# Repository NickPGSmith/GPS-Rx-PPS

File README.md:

# GPS-Rx-PPS
A KiCAD schematic and PCB to buffer/alarm a GPS receiver PPS signal

## Introduction

There are many cheap GPS receiver boards available which provide a serial output and Pulse-Per-Second (PPS) output, typically based on the uBlox 6 or later chip. This board is designed to take the PPS signal from such a receiver and provide buffering, LED drive, and missing pulse alarm (audio and LED).

For a printable schematic, see the file:
- GPS Rx PPS_sch.pdf

For a file to send to a fabricator (eg JLCPCB or PCBWay), use the file:
- Fabrication/GPS Rx PPS.zip

## uBlox Receiver Configuration

The uBlox receiver can be configured via the serial line using the [uCenter](https://www.u-blox.com/en/product/u-center) software. It should generate a 1 Hz outout (timed on falling edge) when GPS synchronisation has been obtained, otherwise a constant high to indicate failure:

View -> Configuration View; to activate change: Send

- TP5 (Timepulse 5)
    - PPS Settings for no GPS lock (use as an "alert" signal:
        - Frequency : 1 Hz
        - Duty Cycle : 0%
    - PPS Settings for GPS Locked:
        - Frequency Locked : 1 Hz
        - Duty Locked : 50%
    - Falling Edge on TOS

To save:
- CFG (Configuration)
    - Select: Save current configuration
    - Select in Devices: 2-I2C-EEPROM

## Circuit Description

The GPS receiver PPS signal is buffered by U2B to provide LED output, U2C to provide buffer drive for an external circuit, and the missing pulse detector built around U1. This will generate a low output after a few seconds of not receiving pulses; the timing can be adjusted by the combination of R3 and C4.

U2D and U2E provide an audio oscillator of a few kHz; its frequency can be adjusted by R9 and C6 to match the resonant frequncy of the piezo sounder used. The oscillator uses U2F as an output buffer/drive, with RV1 preset setting the desired volume.
The oscillations are quenched when Q2 is turned on, ie when the "Not Alarm" output of U1 is high.

PCB Connections:
- CON1: DC Power in (5 V)
- CON2: Power LED
- CON3: Alarm LED
- CON4: PPS in, from GPS received (timing on falling edge)
- CON5: PPS LED
- CON6: PPS out (jumper selects low impendance or 50 Ohm)
- CON7: Alarm sounder out

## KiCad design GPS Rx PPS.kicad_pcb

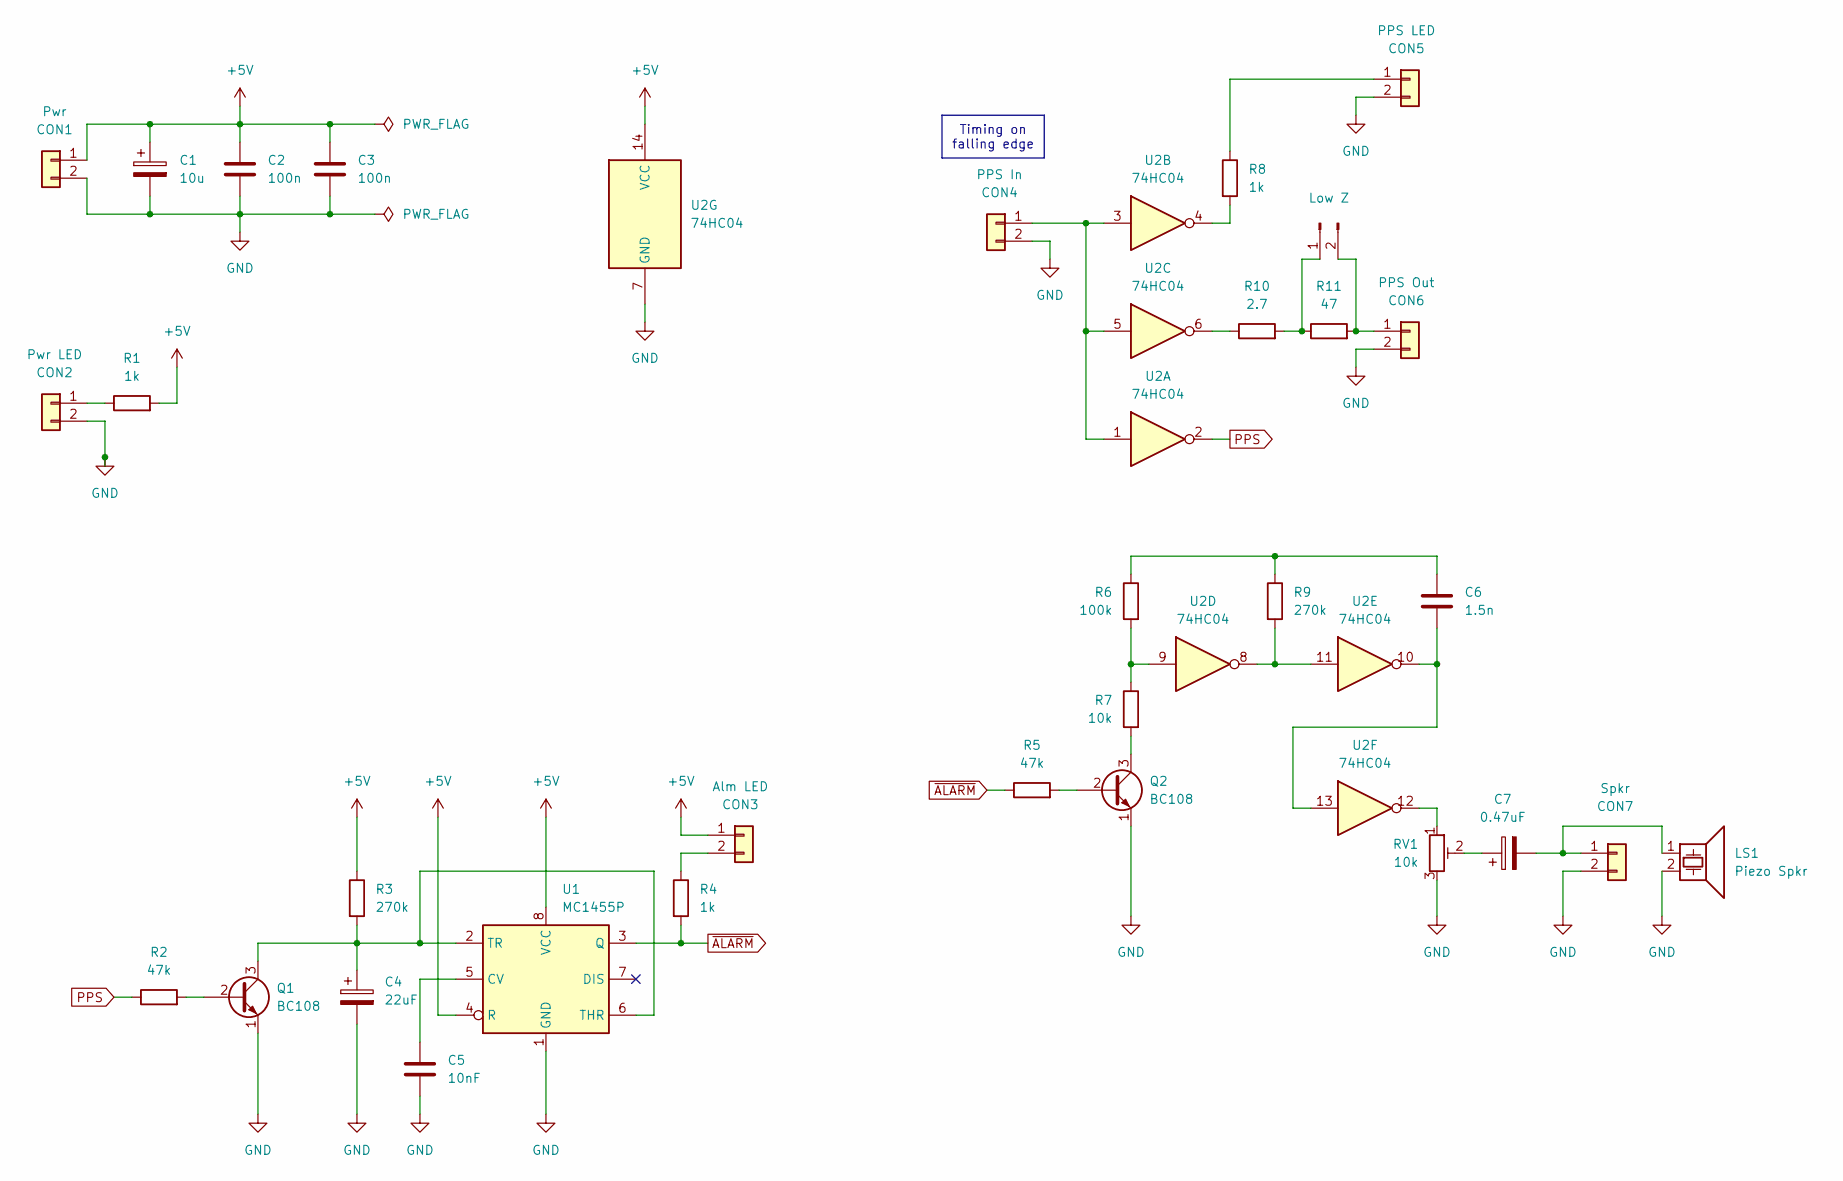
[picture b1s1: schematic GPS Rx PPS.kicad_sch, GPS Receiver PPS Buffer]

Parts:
C1: 10u; CP_Radial_D5.0mm_P2.00mm
C2, C3: 100n; C_Disc_D3.0mm_W1.6mm_P2.50mm
C4: 22uF; CP_Radial_D5.0mm_P2.00mm
C5: 10nF; C_Disc_D4.3mm_W1.9mm_P5.00mm
C6: 1.5n; C_Disc_D3.0mm_W1.6mm_P2.50mm
C7: 0.47uF; CP_Radial_D6.3mm_P2.50mm
CON1: Pwr; PinHeader_1x02_P2.54mm_Vertical
CON2: Pwr LED; PinHeader_1x02_P2.54mm_Vertical
CON3: Alm LED; PinHeader_1x02_P2.54mm_Vertical
CON4: PPS In; PinHeader_1x02_P2.54mm_Vertical
CON5: PPS LED; PinHeader_1x02_P2.54mm_Vertical
CON6: PPS Out; PinHeader_1x02_P2.54mm_Vertical
CON7: Spkr; PinHeader_1x02_P2.54mm_Vertical
J1: Low Z; PinHeader_1x02_P2.54mm_Vertical
LS1: Piezo Spkr; Buzzer_TDK_PS1240P02BT_D12.2mm_H6.5mm
Q1, Q2: BC108; TO-18-3
R1, R4, R8: 1k; R_Axial_DIN0207_L6.3mm_D2.5mm_P2.54mm_Vertical
R2, R5: 47k; R_Axial_DIN0207_L6.3mm_D2.5mm_P2.54mm_Vertical
R3, R9: 270k; R_Axial_DIN0207_L6.3mm_D2.5mm_P2.54mm_Vertical
R6: 100k; R_Axial_DIN0207_L6.3mm_D2.5mm_P2.54mm_Vertical
R7: 10k; R_Axial_DIN0207_L6.3mm_D2.5mm_P2.54mm_Vertical
R10: 2.7; R_Axial_DIN0207_L6.3mm_D2.5mm_P2.54mm_Vertical
R11: 47; R_Axial_DIN0207_L6.3mm_D2.5mm_P2.54mm_Vertical
RV1: 10k; Potentiometer_Piher_PT-6-V_Vertical
U1: MC1455P; DIP-8_W7.62mm_LongPads
U2: 74HC04; CERDIP-14_W7.62mm_SideBrazed_LongPads

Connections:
+5V: C1.1, C2.1, C3.1, CON1.1, CON3.1, R1.2, R3.1, U1.4 (R), U1.8 (VCC), U2.14 (VCC)
GND: C1.2, C2.2, C3.2, C4.2, C5.2, CON1.2, CON2.2, CON4.2, CON5.2, CON6.2, CON7.2, LS1.2, Q1.1 (E), Q2.1 (E), RV1.3, U1.1 (GND), U2.7 (GND)
unnamed: C6.1, R6.1, R9.1
unnamed: C6.2, U2.10, U2.13
unnamed: C7.1, RV1.2
unnamed: CON2.1, R1.1
unnamed: CON3.2, R4.1
unnamed: CON4.1, U2.1, U2.3, U2.5
unnamed: CON5.1, R8.1
unnamed: CON6.1, J1.2, R11.2
unnamed: C7.2, CON7.1, LS1.1
unnamed: J1.1, R10.2, R11.1
unnamed: Q1.2 (B), R2.2
unnamed: C4.1, Q1.3 (C), R3.2, U1.2 (TR), U1.6 (THR)
unnamed: Q2.2 (B), R5.2
unnamed: Q2.3 (C), R7.2
unnamed: R6.2, R7.1, U2.9
unnamed: R8.2, U2.4
unnamed: R9.2, U2.8, U2.11
unnamed: R10.1, U2.6
unnamed: RV1.1, U2.12
unnamed: C5.1, U1.5 (CV)
PPS: R2.1, U2.2
~ALARM: R4.2, R5.1, U1.3 (Q)

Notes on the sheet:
Timing on falling edge

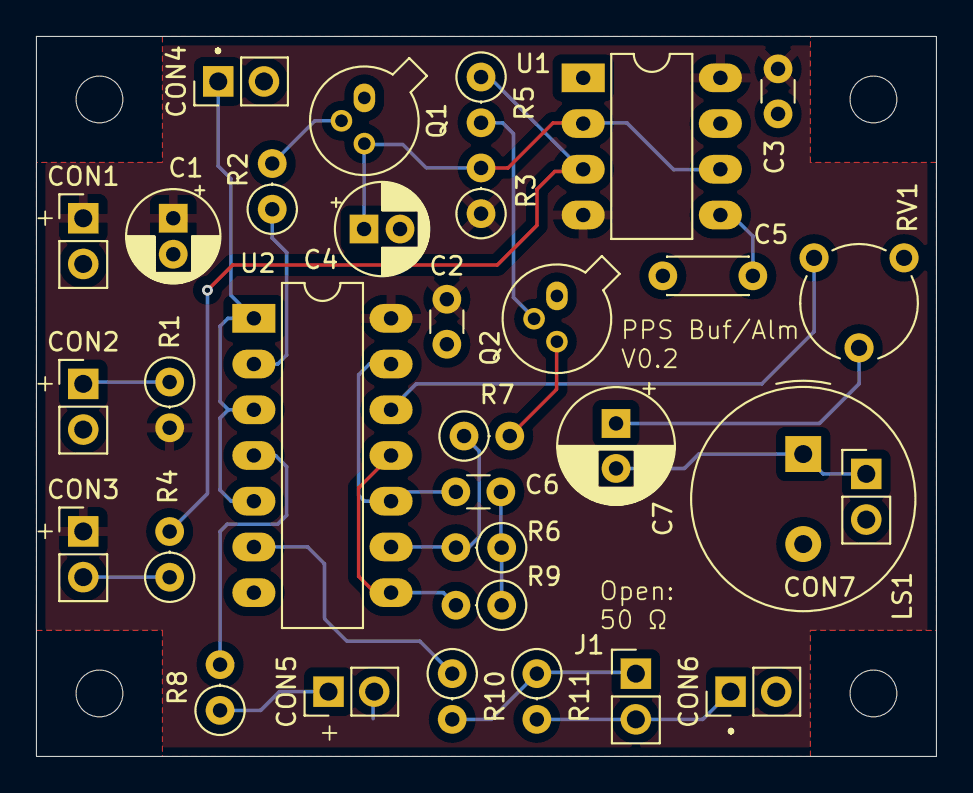
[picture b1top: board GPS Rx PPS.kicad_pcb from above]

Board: 2 copper layers, 50.0 x 40.0 mm, 32 parts (0 on the bottom side), 24 nets.

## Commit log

2024-10-07 V0.2
